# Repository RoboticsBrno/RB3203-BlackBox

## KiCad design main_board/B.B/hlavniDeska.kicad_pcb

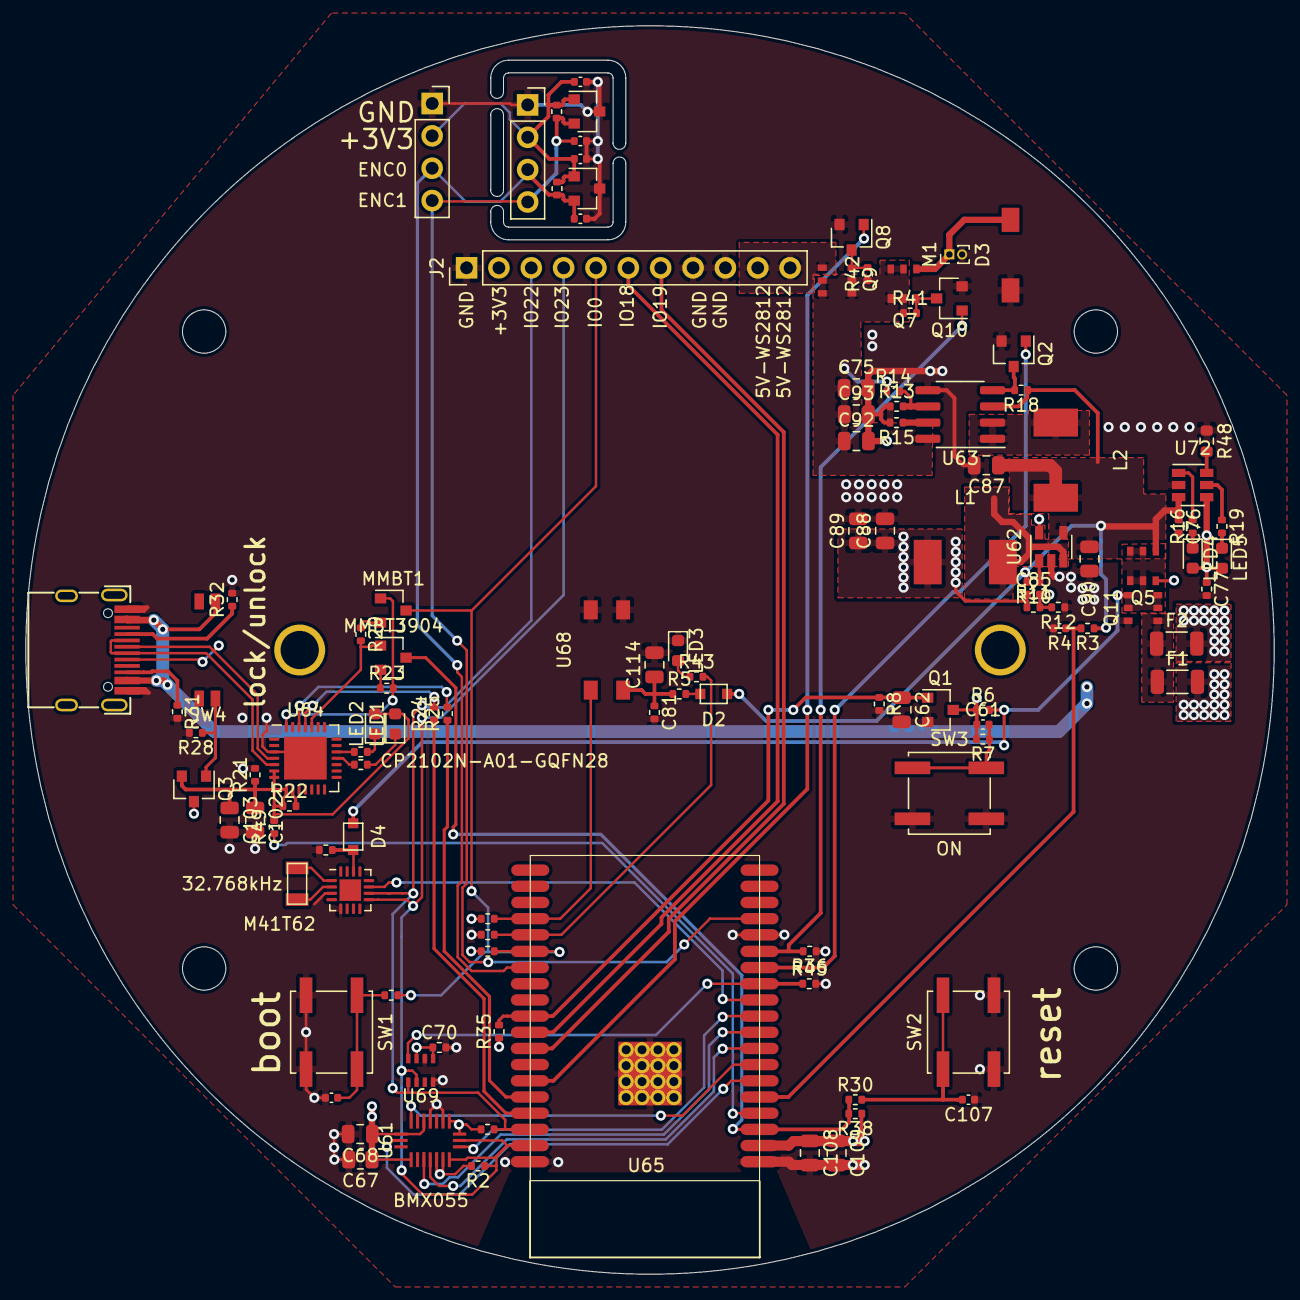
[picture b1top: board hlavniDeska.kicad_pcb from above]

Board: 4 copper layers, 98.0 x 98.0 mm, 117 parts (1 on the bottom side), 77 nets.

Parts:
BT1: Battery_Cell; 18650-holder
C61: 1uf; C_0402_1005Metric
C62, C89, C114: 2.2uf; C_0805_2012Metric
C67: 10uf; R_0805_2012Metric
C68, C102, C108: 0.1uf; C_0805_2012Metric
C69, C70, C76, C77: 1uf; R_0402_1005Metric
C71, C73: 22n; C_0402_1005Metric
C72, C74: 18p/50V; C_0402_1005Metric
C75, C90, C92, C93: 22uf; C_0805_2012Metric
C81: 0.1uf; R_0402_1005Metric
C85: 22nf; C_0402_1005Metric
C87: 4.7uf; C_0805_2012Metric
C88, C103, C109: 10uf; C_0805_2012Metric
C104, C107: 100nf; C_0402_1005Metric
D2, D4: D; SOD-323
D3: SS54; DO-214AC
F1, F2: Polyfuse; L_1206_3216Metric
J1, J4: Conn_01x04; PinSocket_1x04_P2.54mm_Vertical
J2: Conn_01x11; PinHeader_1x11_P2.54mm_Vertical
J5: USB_C_Receptacle_USB2.0; USB_C_Female-16Pin-HPJF
L1, L2: 2.2uH; MWSA0603_6.6x7.1x3.0
LED1, LED2, LED4: RED; LED_0603_1608Metric
LED3: IR; LED_0603_1608Metric
LED5: BLUE; LED_0603_1608Metric
M1: Motor_DC; PinHeader_1x02_P1.00mm_Vertical
MMBT1, MMBT3904: Q_NPN_BCE; SOT-23
Q1, Q2, Q8, Q10: 2N7002; SOT-23
Q3: AO3400A; SOT-23
Q5, Q7, Q9, Q11: SI3447CDV; TSOP-6_1.5x3.0x0.95P
R1, R2, R13: 7.5k; R_0402_1005Metric
R3, R7, R8, R21, R28: 1M; R_0402_1005Metric
R4: 300k; C_0402_1005Metric
R5, R20, R30: 470; R_0402_1005Metric
R6, R10, R18, R41, R42, R45: 100k; R_0402_1005Metric
R11, R46, R47: 47k; R_0402_1005Metric
R12: 15k; R_0402_1005Metric
R14, R15: 56k; R_0402_1005Metric
R16, R19: 1k; R_0402_1005Metric
R22: 1K; R_0402_1005Metric
R23, R29, R33, R34, R35, R36, R37, R38: 12k; R_0402_1005Metric
R24, R25, R26, R27, R43, R49: 220; R_0402_1005Metric
R31, R32: 5.1k; R_0402_1005Metric
R48: 1.5k; R_0603_1608Metric
SW1, SW2, SW3: SW_DIP_x01; SW_Push_1P1T_NO_CK_KSC6xxJ
SW4: SW_DIP_x02; SW-SMD-4
U61: BMX055; LGA_4.5x3
U62: SY8009; SOT-23-5
U63: FP6276; SOP-8_3.76x4.96mm_P1.27mm
U64: CP2102N-A01-GQFN28; QFN-28-1EP_5x5mm_P0.5mm_EP3.35x3.35mm
U65: ESP32-WROVER
U67: M41T62; QFN-16-1EP_3x3mm_P0.5mm_EP1.7x1.7mm
U68: IRM-H936; SMD-4_4.0x5.0x2.54P
U69: SPL06; SMD-8_2x2.5x0.65P
U70, U71: MH253ESO; SOT-23
U72: SE9017; SOT-23-6
Y1: 32.768kHz; SMD-3215_2P

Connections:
+3V3: C67.1, C68.1, C70.1, C71.1, C73.1, C85.1, C88.1, C89.1, C108.1, C109.1, J1.2, J2.2, J4.2, L1.2, Q3.3, R1.2, R2.2, R11.1, R33.1, R35.1, R37.1, R38.1, R46.1, R47.1, U61.3, U61.7, U61.12, U61.13, U61.17, U61.20, U65.2, U69.6, U69.8, U70.1, U71.1
+5V: C75.1, C92.1, C93.1, Q7.1, Q7.2, Q7.5, Q7.6, Q9.1, Q9.2, Q9.5, Q9.6, R14.1, R41.1, R42.1, U63.8
/BAT+: D4.2, Q5.1, Q5.2, Q5.5, Q5.6, Q11.1, Q11.2, Q11.5, Q11.6, R6.2
/ESP3200/5V_USB: C77.1, J5.A4, J5.A9, J5.B4, J5.B9, LED4.2, LED5.2, SW4.2, U72.4
/ESP3200/D+: J5.A6, J5.B6, U64.4
/ESP3200/D-: J5.A7, J5.B7, U64.5
/ESP3200/DTR: MMBT1.1, R23.2, U64.28
/ESP3200/EN: MMBT3904.3, R30.1, R38.2, U65.3
/ESP3200/IO0-up: J2.5, MMBT1.3, R20.1, R33.2, U65.25
/ESP3200/IO2-down: R34.2, R43.2, U65.24
/ESP3200/IO5-up: C62.1, Q1.1, R8.1, R35.2, U65.29
/ESP3200/IO12-down: Q10.1, R36.2, U65.14
/ESP3200/IO14: Q2.1, U65.13
/ESP3200/IO15-up: R37.2, U65.23, U68.3
/ESP3200/IO18: J2.6, U65.30
/ESP3200/IO19: J2.7, U65.31
/ESP3200/IO21: Q8.1, U65.33
/ESP3200/IO22: J2.3, R1.1, U65.36, U67.10, U69.4
/ESP3200/IO23: J2.4, R2.1, U61.11, U65.37, U67.9, U69.3
/ESP3200/IO25: U61.10, U65.10
/ESP3200/IO26: U65.11, U67.11
/ESP3200/IO27: R45.1, U65.12, U69.5
/ESP3200/IO32: U61.14, U65.8
/ESP3200/IO33: U61.15, U65.9
/ESP3200/IO34: U61.19, U65.6
/ESP3200/IO35: U61.1, U65.7
/ESP3200/IO36: R49.1, U65.4
/ESP3200/IO39: R3.2, R4.1, U65.5
/ESP3200/RTS: MMBT3904.1, R29.2, U64.24
/ESP3200/RX-esp: R25.1, U65.34
/ESP3200/TX-esp: R24.1, U65.35
/expanz00/5V-WS2812: J2.10, J2.11, Q9.4
/expanz00/ENC_OUT_0: C72.1, J1.3, J4.3, R46.2, U65.26, U70.2
/expanz00/ENC_OUT_1: C74.1, J1.4, J4.4, R47.2, U65.16, U71.2
GND: BT1.2, BT1.4, C62.2, C67.2, C68.2, C69.2, C70.2, C71.2, C72.2, C73.2, C74.2, C75.2, C76.2, C77.2, C81.2, C87.2, C88.2, C89.2, C90.2, C92.2, C93.2, C102.2, C103.2, C104.1, C107.1, C108.2, C109.2, C114.2, D3.2, J1.1, J2.1, J2.8, J2.9, J4.1, J5.A1, J5.A12, J5.B1, J5.B12, LED3.1, M1.2, Q1.2, Q2.2, Q8.2, Q10.2, Q11.3, R4.2, R8.2, R12.1, R13.1, R15.2, R21.2, R28.2, R31.2, R32.2, R34.1, R36.1, R45.2, R48.1, SW1.1, SW2.1, SW3.1, U61.4, U61.6, U62.2, U63.5, U64.3, U64.29, U65.1, U65.15, U65.38, U65.39, U67.3, U67.5, U68.1, U68.2, U69.1, U69.7, U70.3, U71.3, U72.2
LX: L2.2, U63.1, U63.2
unnamed: BT1.1, F2.2
unnamed: BT1.3, F1.2
unnamed: C61.1, Q1.3, Q5.3, R6.1, R7.2
unnamed: C61.2, R7.1, SW3.2
unnamed: C69.1, D4.1, U67.14
unnamed: C85.2, R11.2, R12.2, U62.5
unnamed: C102.1, C103.1, LED1.2, LED2.2, Q3.2, R21.1, R22.1, R49.2, U64.6, U64.7, U64.8
unnamed: C104.2, R20.2, SW1.2
unnamed: C107.2, R30.2, SW2.2
unnamed: C81.1, C114.1, R5.1, U68.4
unnamed: D2.1, R5.2
unnamed: D3.1, M1.1, Q7.4
unnamed: F1.1, F2.1, Q11.4
unnamed: J5.A5, R32.1
unnamed: J5.B5, R31.1
unnamed: L1.1, U62.3
unnamed: LED1.1, R26.1
unnamed: LED2.1, R27.1
unnamed: LED3.2, R43.1
unnamed: LED4.1, R16.1
unnamed: LED5.1, R19.2
unnamed: MMBT1.2, R29.1
unnamed: MMBT3904.2, R23.1
unnamed: Q2.3, R18.2, U63.4
unnamed: Q3.1, R28.1, SW4.3
unnamed: Q8.3, Q9.3, R42.2
unnamed: Q7.3, Q10.3, R41.2
unnamed: R10.1, U62.1
unnamed: R13.2, R14.2, U63.6
unnamed: R15.1, U63.7
unnamed: R16.2, U72.1
unnamed: R19.1, U72.5
unnamed: R22.2, U64.9
unnamed: R24.2, U64.25
unnamed: R25.2, U64.26
unnamed: R26.2, U64.18
unnamed: R27.2, U64.19
unnamed: R48.2, U72.6
unnamed: U67.1, Y1.1
unnamed: U67.2, Y1.2
VCC: C76.1, C87.1, C90.1, D2.2, L2.1, Q5.4, R3.1, R10.2, R18.1, U62.4, U63.3, U72.3

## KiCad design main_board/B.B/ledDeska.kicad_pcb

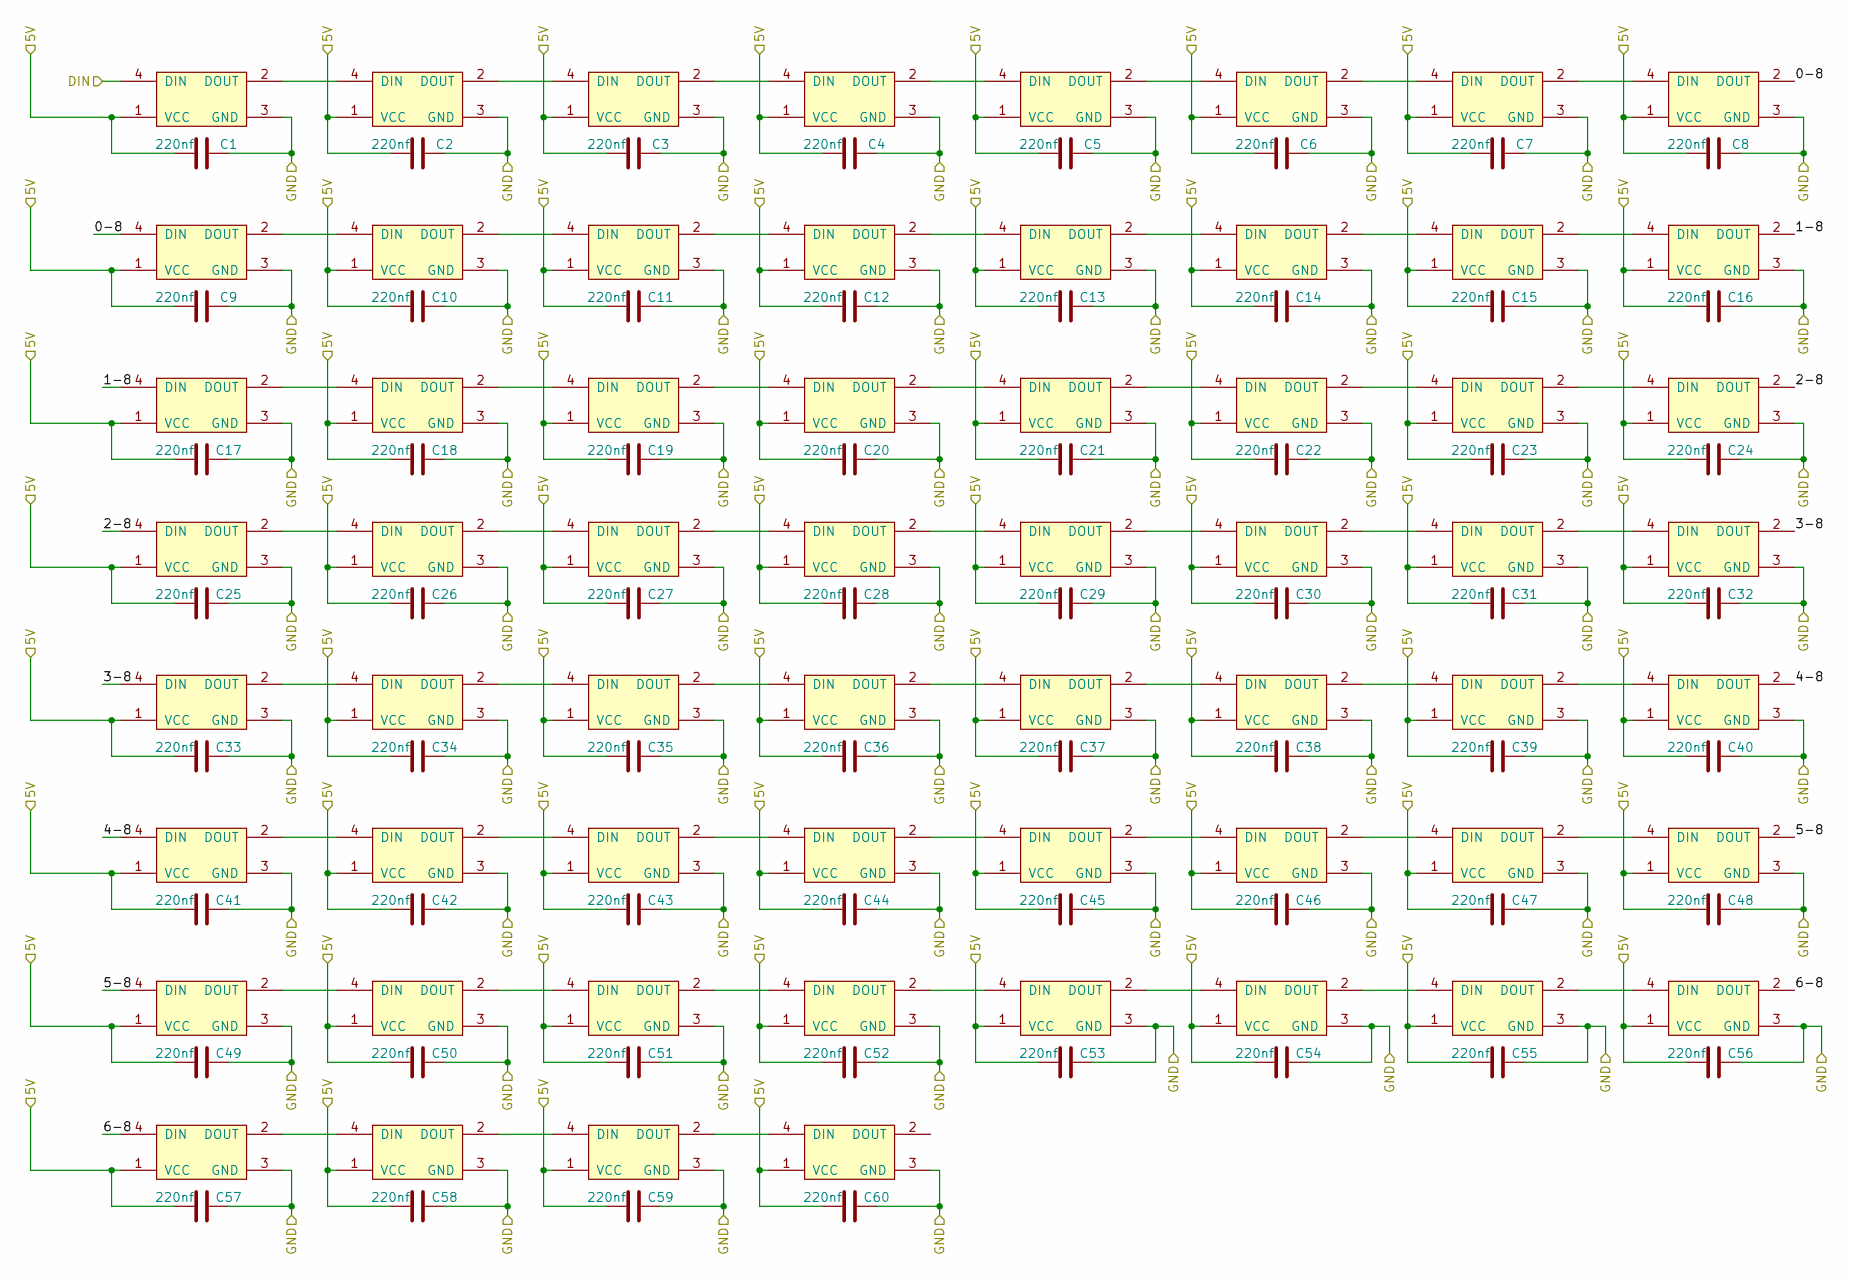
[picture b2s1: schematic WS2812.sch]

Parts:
C1, C2, C3, C4, C5, C6, C7, C8, C9, C10, C11, C12, C13, C14, C15, C16, C17, C18, C19, C20, C21, C22, C23, C24, C25, C26, C27, C28, C29, C30, C31, C32, C33, C34, C35, C36, C37, C38, C39, C40, C41, C42, C43, C44, C45, C46, C47, C48, C49, C50, C51, C52, C53, C54, C55, C56, C57, C58, C59, C60: 220nf; C_0402_1005Metric; LCSC C16772
U1, U2, U3, U4, U5, U6, U7, U8, U9, U10, U11, U12, U13, U14, U15, U16, U17, U18, U19, U20, U21, U22, U23, U24, U25, U26, U27, U28, U29, U30, U31, U32, U33, U34, U35, U36, U37, U38, U39, U40, U41, U42, U43, U44, U45, U46, U47, U48, U49, U50, U51, U52, U53, U54, U55, U56, U57, U58, U59, U60: WS2812; LCSC C114583

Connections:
/next-board00/5V: C1.2, C2.2, C3.2, C4.2, C5.2, C6.2, C7.2, C8.2, C9.2, C10.2, C11.2, C12.2, C13.2, C14.2, C15.2, C16.2, C17.2, C18.2, C19.2, C20.2, C21.2, C22.2, C23.2, C24.2, C25.2, C26.2, C27.2, C28.2, C29.2, C30.2, C31.2, C32.2, C33.2, C34.2, C35.2, C36.2, C37.2, C38.2, C39.2, C40.2, C41.2, C42.2, C43.2, C44.2, C45.2, C46.2, C47.2, C48.2, C49.2, C50.2, C51.2, C52.2, C53.2, C54.2, C55.2, C56.2, C57.2, C58.2, C59.2, C60.2, U1.1 (VCC), U2.1 (VCC), U3.1 (VCC), U4.1 (VCC), U5.1 (VCC), U6.1 (VCC), U7.1 (VCC), U8.1 (VCC), U9.1 (VCC), U10.1 (VCC), U11.1 (VCC), U12.1 (VCC), U13.1 (VCC), U14.1 (VCC), U15.1 (VCC), U16.1 (VCC), U17.1 (VCC), U18.1 (VCC), U19.1 (VCC), U20.1 (VCC), U21.1 (VCC), U22.1 (VCC), U23.1 (VCC), U24.1 (VCC), U25.1 (VCC), U26.1 (VCC), U27.1 (VCC), U28.1 (VCC), U29.1 (VCC), U30.1 (VCC), U31.1 (VCC), U32.1 (VCC), U33.1 (VCC), U34.1 (VCC), U35.1 (VCC), U36.1 (VCC), U37.1 (VCC), U38.1 (VCC), U39.1 (VCC), U40.1 (VCC), U41.1 (VCC), U42.1 (VCC), U43.1 (VCC), U44.1 (VCC), U45.1 (VCC), U46.1 (VCC), U47.1 (VCC), U48.1 (VCC), U49.1 (VCC), U50.1 (VCC), U51.1 (VCC), U52.1 (VCC), U53.1 (VCC), U54.1 (VCC), U55.1 (VCC), U56.1 (VCC), U57.1 (VCC), U58.1 (VCC), U59.1 (VCC), U60.1 (VCC); also elsewhere on the board
/next-board00/GND: C1.1, C2.1, C3.1, C4.1, C5.1, C6.1, C7.1, C8.1, C9.1, C10.1, C11.1, C12.1, C13.1, C14.1, C15.1, C16.1, C17.1, C18.1, C19.1, C20.1, C21.1, C22.1, C23.1, C24.1, C25.1, C26.1, C27.1, C28.1, C29.1, C30.1, C31.1, C32.1, C33.1, C34.1, C35.1, C36.1, C37.1, C38.1, C39.1, C40.1, C41.1, C42.1, C43.1, C44.1, C45.1, C46.1, C47.1, C48.1, C49.1, C50.1, C51.1, C52.1, C53.1, C54.1, C55.1, C56.1, C57.1, C58.1, C59.1, C60.1, U1.3 (GND), U2.3 (GND), U3.3 (GND), U4.3 (GND), U5.3 (GND), U6.3 (GND), U7.3 (GND), U8.3 (GND), U9.3 (GND), U10.3 (GND), U11.3 (GND), U12.3 (GND), U13.3 (GND), U14.3 (GND), U15.3 (GND), U16.3 (GND), U17.3 (GND), U18.3 (GND), U19.3 (GND), U20.3 (GND), U21.3 (GND), U22.3 (GND), U23.3 (GND), U24.3 (GND), U25.3 (GND), U26.3 (GND), U27.3 (GND), U28.3 (GND), U29.3 (GND), U30.3 (GND), U31.3 (GND), U32.3 (GND), U33.3 (GND), U34.3 (GND), U35.3 (GND), U36.3 (GND), U37.3 (GND), U38.3 (GND), U39.3 (GND), U40.3 (GND), U41.3 (GND), U42.3 (GND), U43.3 (GND), U44.3 (GND), U45.3 (GND), U46.3 (GND), U47.3 (GND), U48.3 (GND), U49.3 (GND), U50.3 (GND), U51.3 (GND), U52.3 (GND), U53.3 (GND), U54.3 (GND), U55.3 (GND), U56.3 (GND), U57.3 (GND), U58.3 (GND), U59.3 (GND), U60.3 (GND); also elsewhere on the board
/next-board00/WS2812: U1.4 (DIN); also elsewhere on the board
/next-board00/WS281200/0-8: U8.2 (DOUT), U9.4 (DIN)
/next-board00/WS281200/1-8: U16.2 (DOUT), U17.4 (DIN)
/next-board00/WS281200/2-8: U24.2 (DOUT), U25.4 (DIN)
/next-board00/WS281200/3-8: U32.2 (DOUT), U33.4 (DIN)
/next-board00/WS281200/4-8: U40.2 (DOUT), U41.4 (DIN)
/next-board00/WS281200/5-8: U48.2 (DOUT), U49.4 (DIN)
/next-board00/WS281200/6-8: U56.2 (DOUT), U57.4 (DIN)
unnamed: U1.2 (DOUT), U2.4 (DIN)
unnamed: U2.2 (DOUT), U3.4 (DIN)
unnamed: U3.2 (DOUT), U4.4 (DIN)
unnamed: U4.2 (DOUT), U5.4 (DIN)
unnamed: U5.2 (DOUT), U6.4 (DIN)
unnamed: U6.2 (DOUT), U7.4 (DIN)
unnamed: U7.2 (DOUT), U8.4 (DIN)
unnamed: U10.2 (DOUT), U11.4 (DIN)
unnamed: U9.2 (DOUT), U10.4 (DIN)
unnamed: U11.2 (DOUT), U12.4 (DIN)
unnamed: U12.2 (DOUT), U13.4 (DIN)
unnamed: U13.2 (DOUT), U14.4 (DIN)
unnamed: U14.2 (DOUT), U15.4 (DIN)
unnamed: U15.2 (DOUT), U16.4 (DIN)
unnamed: U17.2 (DOUT), U18.4 (DIN)
unnamed: U18.2 (DOUT), U19.4 (DIN)
unnamed: U19.2 (DOUT), U20.4 (DIN)
unnamed: U20.2 (DOUT), U21.4 (DIN)
unnamed: U21.2 (DOUT), U22.4 (DIN)
unnamed: U22.2 (DOUT), U23.4 (DIN)
unnamed: U23.2 (DOUT), U24.4 (DIN)
unnamed: U25.2 (DOUT), U26.4 (DIN)
unnamed: U26.2 (DOUT), U27.4 (DIN)
unnamed: U27.2 (DOUT), U28.4 (DIN)
unnamed: U28.2 (DOUT), U29.4 (DIN)
unnamed: U29.2 (DOUT), U30.4 (DIN)
unnamed: U30.2 (DOUT), U31.4 (DIN)
unnamed: U31.2 (DOUT), U32.4 (DIN)
unnamed: U33.2 (DOUT), U34.4 (DIN)
unnamed: U34.2 (DOUT), U35.4 (DIN)
unnamed: U35.2 (DOUT), U36.4 (DIN)
unnamed: U36.2 (DOUT), U37.4 (DIN)
unnamed: U37.2 (DOUT), U38.4 (DIN)
unnamed: U38.2 (DOUT), U39.4 (DIN)
unnamed: U39.2 (DOUT), U40.4 (DIN)
unnamed: U41.2 (DOUT), U42.4 (DIN)
unnamed: U42.2 (DOUT), U43.4 (DIN)
unnamed: U43.2 (DOUT), U44.4 (DIN)
unnamed: U44.2 (DOUT), U45.4 (DIN)
unnamed: U45.2 (DOUT), U46.4 (DIN)
unnamed: U46.2 (DOUT), U47.4 (DIN)
unnamed: U47.2 (DOUT), U48.4 (DIN)
unnamed: U49.2 (DOUT), U50.4 (DIN)
unnamed: U50.2 (DOUT), U51.4 (DIN)
unnamed: U51.2 (DOUT), U52.4 (DIN)
unnamed: U52.2 (DOUT), U53.4 (DIN)
unnamed: U53.2 (DOUT), U54.4 (DIN)
unnamed: U54.2 (DOUT), U55.4 (DIN)
unnamed: U55.2 (DOUT), U56.4 (DIN)
unnamed: U57.2 (DOUT), U58.4 (DIN)
unnamed: U58.2 (DOUT), U59.4 (DIN)
unnamed: U59.2 (DOUT), U60.4 (DIN)

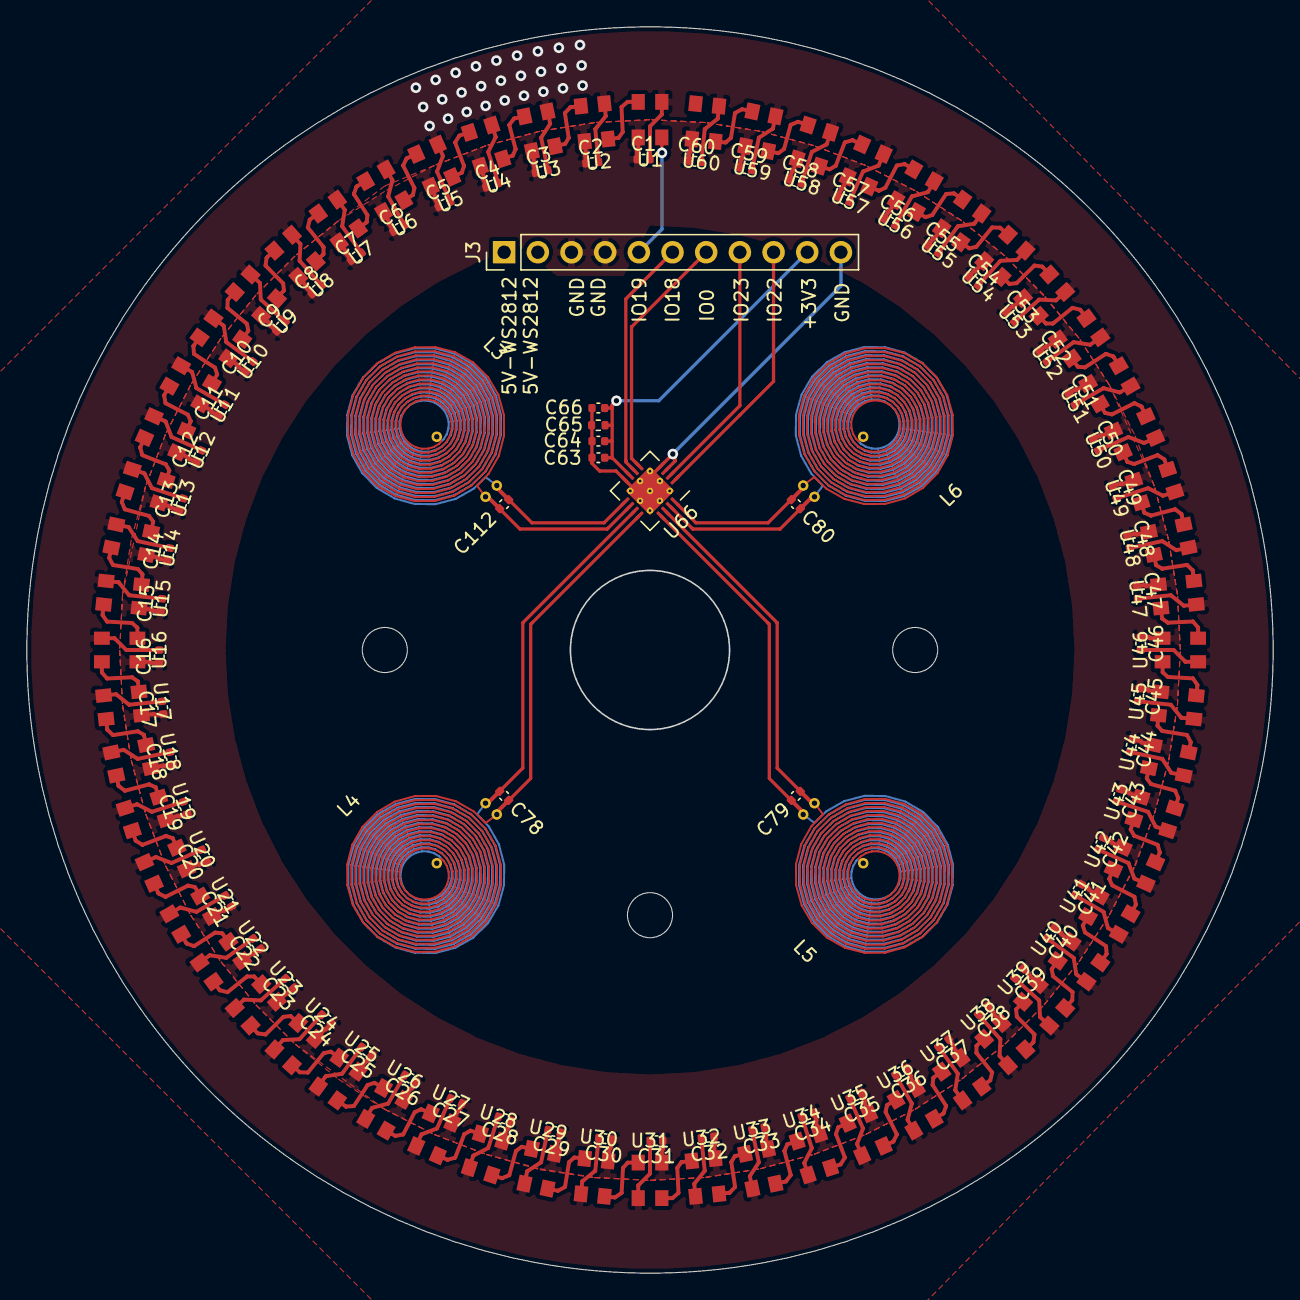
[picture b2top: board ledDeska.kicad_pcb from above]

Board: 2 copper layers, 94.0 x 94.0 mm, 134 parts (0 on the bottom side), 76 nets.

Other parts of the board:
C63, C64: 10nf; C_0402_1005Metric
C65: 0.1uf; R_0402_1005Metric
C66: 1uf; C_0402_1005Metric
C78, C79, C80, C112: 1000pf; C_0402_1005Metric
J3: Conn_01x11; PinHeader_1x11_P2.54mm_Vertical
L3, L4, L5, L6: L; coil
U66: LDC1314; WQFN-16-1EP_4x4mm_P0.5mm_EP2.6x2.6mm_ThermalVias

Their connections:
/next-board00/3V3: C63.1, C64.1, C65.1, C66.2, J3.10, U66.7
/next-board00/5V: J3.1, J3.2; also elsewhere on the board
/next-board00/GND: J3.3, J3.4; also elsewhere on the board
/next-board00/INT: J3.7, U66.5
/next-board00/LDC-GND: C63.2, C64.2, C65.2, C66.1, J3.11, U66.3, U66.4, U66.8, U66.17
/next-board00/SCL: J3.9, U66.1
/next-board00/SDA: J3.8, U66.2
/next-board00/SHUTDOWN: J3.6, U66.6
/next-board00/WS2812: J3.5; also elsewhere on the board
unnamed: C78.1, L4.1, U66.12
unnamed: C78.2, L4.2, U66.11
unnamed: C79.1, L5.1, U66.14
unnamed: C79.2, L5.2, U66.13
unnamed: C80.1, L6.1, U66.16
unnamed: C80.2, L6.2, U66.15
unnamed: C112.1, L3.1, U66.10
unnamed: C112.2, L3.2, U66.9
